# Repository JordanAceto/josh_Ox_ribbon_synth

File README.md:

# josh_Ox_ribbon_synth
Ribbon synth for [Josh Oxford](https://www.joshoxford.com/)

## Main Features 
- Single VCO with two sub-oscillators
- Transformer/diode based Ring Modulator
- Dual State-Variable Filter
- Bucket brigade Analog Delay with modulation
- Envelope VCA
- Volume VCA
- Three ADSR's
- Sample and Hold
- Flexible gate control
- Versatile Modulation Oscillator
- Ribbon controller with quantizer

## Status:

A complete synthesizer has been built with the current documents here. This instrument has been road tested on a few gigs. The current files represent a working instrument.

There are a few small PCB kludges required, and some potential future enhancements.
See the `github Issues` and `github Discussions` for little things that could be improved and an idea of what may change in the future.

The synth is constructed with semi-independent PCBs and panels for the major circuit blocks, which allows for gradually upgrading the components over time.

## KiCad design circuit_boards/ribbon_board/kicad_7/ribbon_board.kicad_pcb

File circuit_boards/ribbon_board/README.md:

# ribbon_board

## [SCHEMATIC](https://github.com/JordanAceto/josh_Ox_ribbon_synth/blob/master/circuit_boards/ribbon_board/docs/ribbon_board_schematic.pdf)

Digital ribbon controller, gate combiner, and VCA control scaler

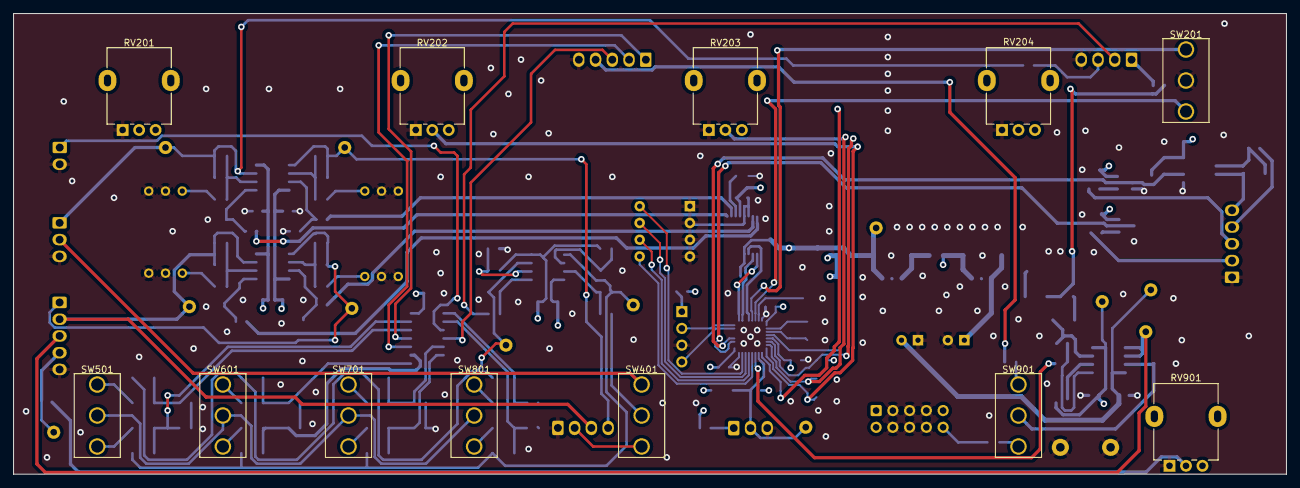
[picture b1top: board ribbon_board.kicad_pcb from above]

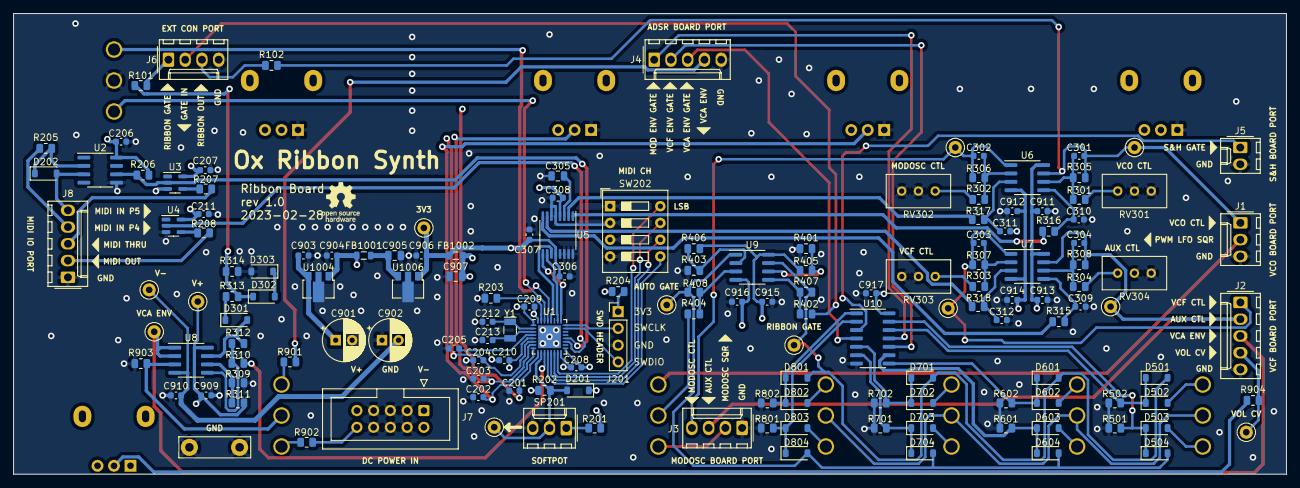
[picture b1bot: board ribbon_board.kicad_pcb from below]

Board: 4 copper layers, 193.0 x 69.8 mm, 165 parts (153 on the bottom side), 105 nets.

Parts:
C201, C202, C203, C204, C205, C206, C207, C208, C209, C210, C211, C301, C302, C303, C304, C306, C307, C308, C309, C310, C311, C312, C903, C904, C906, C909, C910, C911, C912, C913, C914, C915, C916, C917: 100n; C_0603_1608Metric
C212, C213: 4p3; C_0603_1608Metric
C305, C907: 1u; C_0805_2012Metric
C901, C902: 10u; CP_Radial_D6.3mm_P2.50mm
C905: 2u2; C_0805_2012Metric
D201: DNF; D_SOD-123
D202, D301, D501, D502, D503, D504, D601, D602, D603, D604, D701, D702, D703, D704, D801, D802, D803, D804: 1N4148W; D_SOD-123
D302, D303: 5v1; D_SOD-123
FB1001, FB1002: 100R @ 100MHz; L_0805_2012Metric
J1: VCO_port; Molex_KK-254_AE-6410-03A_1x03_P2.54mm_Vertical
J2: VCF_port; Molex_KK-254_AE-6410-05A_1x05_P2.54mm_Vertical
J3: mod_osc_port; Molex_KK-254_AE-6410-04A_1x04_P2.54mm_Vertical
J4: ADSR_port; Molex_KK-254_AE-6410-05A_1x05_P2.54mm_Vertical
J5: S&H_port; Molex_KK-254_AE-6410-02A_1x02_P2.54mm_Vertical
J6: ext_port; Molex_KK-254_AE-6410-04A_1x04_P2.54mm_Vertical
J7: power_entry; IDC-Header_2x05_P2.54mm_Vertical
J8: MIDI_IO_port; Molex_KK-254_AE-6410-05A_1x05_P2.54mm_Vertical
J201: SWD_header; PinHeader_1x04_P2.54mm_Vertical
R101, R102, R204, R313, R904: 1k; R_0805_2012Metric
R201: 22; R_0805_2012Metric
R202: DNF; R_0805_2012Metric
R203, R206, R309, R310, R401, R402, R403, R404: 10k; R_0805_2012Metric
R205: 220; R_0805_2012Metric
R207, R208: 47; R_0805_2012Metric
R301, R302, R303, R304: 20k; R_0805_2012Metric
R305, R306, R307, R308: 68k; R_0805_2012Metric
R311, R314, R405, R406, R501, R502, R601, R602, R701, R702, R801, R802, R903: 100k; R_0805_2012Metric
R312, R407, R408: 1M2; R_0805_2012Metric
R315, R316, R317, R318: 12k; R_0805_2012Metric
R901: 82k; R_0805_2012Metric
R902: 200k; R_0805_2012Metric
RV201: 10k; Potentiometer_Alpha_RD901F-40-00D_Single_Vertical
RV202, RV203, RV204: 10k c.d.; Potentiometer_Alpha_RD901F-40-00D_Single_Vertical
RV301, RV302, RV303, RV304: 5k; Potentiometer_Bourns_3296W_Vertical
RV901: 100k; Potentiometer_Alpha_RD901F-40-00D_Single_Vertical
SP201: softpot; Molex_KK-254_AE-6410-03A_1x03_P2.54mm_Vertical
SW201, SW501, SW601, SW701, SW801: SW_SPDT_MSM; SPDT_mini_toggle
SW202: MIDI_CH; SW_DIP_SPSTx04_Slide_9.78x12.34mm_W7.62mm_P2.54mm
SW401, SW901: SW_SPDT; SPDT_mini_toggle
TP201: RAW_RIBBON; TestPoint_Keystone_5000-5004_Miniature
TP301: VCO_RIBBON; TestPoint_Keystone_5000-5004_Miniature
TP302: MODOSC_RIBBON; TestPoint_Keystone_5000-5004_Miniature
TP303: VCF_RIBBON; TestPoint_Keystone_5000-5004_Miniature
TP304: AUX_CV; TestPoint_Keystone_5000-5004_Miniature
TP401: rib_gate; TestPoint_Keystone_5000-5004_Miniature
TP402: auto_gate; TestPoint_Keystone_5000-5004_Miniature
TP901: VCA_ADSR_CV; TestPoint_Keystone_5000-5004_Miniature
TP902: VCA_VOL_CV; TestPoint_Keystone_5000-5004_Miniature
TP1001: V+; TestPoint_Keystone_5000-5004_Miniature
TP1002: V-; TestPoint_Keystone_5000-5004_Miniature
TP1003: GND; TestPoint_Bridge_Pitch7.62mm_Drill1.3mm
TP1004: 3v3; TestPoint_Keystone_5000-5004_Miniature
U1: STM32L412K8Ux; QFN-32-1EP_5x5mm_P0.5mm_EP3.45x3.45mm
U2: VO0600T; SOIC-8_3.9x4.9mm_P1.27mm
U3, U4: SN74LV1T34DBV; SOT-23-5
U5: DAC8164; TSSOP-16_4.4x5mm_P0.65mm
U6, U7, U8, U9: TL072; SOIC-8_3.9x4.9mm_P1.27mm
U10: 4081; SOIC-14_3.9x8.7mm_P1.27mm
U1004: L78L05_SOT89; SOT-89-3
U1006: L78L33_SOT89; SOT-89-3
Y1: 32_768KHZ; Crystal_SMD_MicroCrystal_CC7V-T1A-2Pin_3.2x1.5mm

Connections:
+3.3V: C206.1, C207.1, C208.1, C209.1, C211.1, C306.1, C307.1, C906.1, D201.1 (K), FB1002.1, R204.1, R206.1, TP1004.1, U1.1 (VDD), U1.17 (VDD), U2.8 (VCC), U3.5 (VCC), U4.5 (VCC), U5.12 (IOVDD), U1006.1 (OUT)
+3.3VA: C210.1, C308.1, C907.1, FB1002.2, R201.1, RV201.3, RV202.3, RV203.3, RV204.3, U1.5 (VDDA), U5.4 (AVDD)
+5V: C904.1, FB1001.1, R202.1, RV901.3, U1004.1 (OUT)
+15V: C901.1, C903.1, C909.1, C911.1, C913.1, C915.1, C917.1, J7.9, J7.10, R311.2, R405.2, R406.2, R902.1, SW501.2, SW601.2, SW701.2, SW801.2, TP1001.1, U6.8 (V+), U7.8 (V+), U8.8 (V+), U9.8 (V+), U10.14 (VDD), U1004.3 (IN)
-15V: C902.2, C910.2, C912.2, C914.2, C916.2, J7.1, J7.2, TP1002.1, U6.4 (V-), U7.4 (V-), U8.4 (V-), U9.4 (V-)
/EXT_GATE_IN_NORMAL_TO_RIBBON_GATE: J6.2, R402.1
/MOD_OSC_SQR: J3.2, SW401.1 (A)
/OPT_VCF_BBD_CV: C304.2, J2.2, J3.3, R308.2, TP304.1, U7.7
/PWM_LFO_SQR: J1.2, SW401.3 (C)
/VCA_ADSR: J4.4, R901.1
/VCA_ENV_CV: J2.3, TP901.1, U8.1, U8.2 (-)
/VCA_VOL_CV: J2.4, R904.2, TP902.1
/VCO_RIBBON_CTL: C301.2, J1.1, R102.2, R305.2, TP301.1, U6.7
/digital_ribbon_control/DELAY_LEV: C204.1, RV204.2, U1.6 (PA0)
/digital_ribbon_control/GATE_3V3: R310.1, U1.11 (PA5)
/digital_ribbon_control/MIDI_CH_0: SW202.8, U1.15 (PB1)
/digital_ribbon_control/MIDI_CH_1: SW202.7, U1.14 (PB0)
/digital_ribbon_control/MIDI_CH_2: SW202.6, U1.13 (PA7)
/digital_ribbon_control/MIDI_CH_3: SW202.5, U1.12 (PA6)
/digital_ribbon_control/MIDI_IN_P4: J8.4, R205.1
/digital_ribbon_control/MIDI_IN_P5: D202.2 (A), J8.5, U2.3 (C)
/digital_ribbon_control/MIDI_OUT: J8.2, R208.2
/digital_ribbon_control/MIDI_RX: R206.2, U1.20 (PA10), U2.6 (VO), U3.2 (A)
/digital_ribbon_control/MIDI_THRU: J8.3, R207.2
/digital_ribbon_control/MIDI_TX: U1.19 (PA9), U4.2 (A)
/digital_ribbon_control/MODE_SW_1: SW201.1, U1.29 (PB6)
/digital_ribbon_control/MODE_SW_2: SW201.3, U1.30 (PB7)
/digital_ribbon_control/MODOSC_LEV: C202.1, RV202.2, U1.8 (PA2)
/digital_ribbon_control/RAW_RIBBON: D201.2 (A), R202.2, SP201.2, TP201.1, U1.10 (PA4)
/digital_ribbon_control/SPI_CS: U1.25 (PA15), U5.9 (~SYNC)
/digital_ribbon_control/SPI_SCK: U1.26 (PB3), U5.10 (SCLK)
/digital_ribbon_control/SPI_SDO: U1.28 (PB5), U5.11 (DIN)
/digital_ribbon_control/SYS_SWCLK: J201.2, U1.24 (PA14)
/digital_ribbon_control/SYS_SWDIO: J201.4, U1.23 (PA13)
/digital_ribbon_control/VCF_LEV: C203.1, RV203.2, U1.7 (PA1)
/digital_ribbon_control/VCO_LEV: C201.1, RV201.2, U1.9 (PA3)
/gate_controller/MOD_ENV_GATE: J4.1, U10.11
/gate_controller/S&H_GATE: J5.1, U10.3
/gate_controller/VCA_ADSR_gate_logic/AUTO_GATE: D504.2 (A), D604.2 (A), D704.2 (A), D804.2 (A), R408.2, TP402.1, U9.1
/gate_controller/VCA_ADSR_gate_logic/RIBBON_GATE: D501.2 (A), D601.2 (A), D701.2 (A), D801.2 (A), R407.2, TP401.1, U9.7
/gate_controller/VCA_ENV_GATE: J4.3, U10.4
/gate_controller/VCF_ENV_GATE: J4.2, U10.10
/ribbon_scalers/GATE: D302.1 (K), R101.2, R313.2, R314.1
/ribbon_scalers/MODOSC_CTL_OUT: C302.2, J3.4, R306.2, TP302.1, U6.1
/ribbon_scalers/VCF_CTL_OUT: C303.2, J2.1, R307.2, TP303.1, U7.1
GND: C201.2, C202.2, C203.2, C204.2, C205.1, C206.2, C207.2, C208.2, C209.2, C210.2, C211.2, C212.1, C213.1, C305.2, C306.2, C307.2, C308.2, C309.1, C310.1, C311.1, C312.1, C901.2, C902.1, C903.2, C904.2, C905.2, C906.2, C907.2, C909.2, C910.1, C911.2, C912.1, C913.2, C914.1, C915.2, C916.1, C917.2, D303.2 (A), J1.3, J2.5, J3.1, J4.5, J5.2, J6.4, J7.3, J7.4, J7.5, J7.6, J7.7, J7.8, J8.1, J201.3, R203.1, R309.1, R314.2, R401.1, R403.1, R501.2, R502.2, R601.2, R602.2, R701.2, R702.2, R801.2, R802.2, R903.1, RV201.1, RV202.1, RV203.1, RV204.1, RV301.2, RV301.3, RV302.2, RV302.3, RV303.2, RV303.3, RV304.2, RV304.3, RV901.1, SP201.3, SW201.2, SW202.1, SW202.2, SW202.3, SW202.4, TP1003.1, U1.16 (VSS), U1.32 (VSS), U1.33 (VSS), U2.5 (GND), U3.3 (GND), U4.3 (GND), U5.5 (VREFL), U5.6 (GND), U5.13 (A0), U5.14 (A1), U5.15 (~ENABLE), U5.16 (LDAC), U10.7 (VSS), U1004.2 (GND), U1006.2 (GND)
unnamed: D202.1 (K), R205.2, U2.2 (A)
unnamed: D301.2 (A), R312.2, U8.7
unnamed: D301.1 (K), R313.1
unnamed: D302.2 (A), D303.1 (K)
unnamed: D501.1 (K), D502.1 (K), R502.1, U10.12
unnamed: D502.2 (A), SW501.3
unnamed: D503.2 (A), SW501.1
unnamed: D503.1 (K), D504.1 (K), R501.1, U10.13
unnamed: D601.1 (K), D602.1 (K), R602.1, U10.8
unnamed: D602.2 (A), SW601.3
unnamed: D603.2 (A), SW601.1
unnamed: D603.1 (K), D604.1 (K), R601.1, U10.9
unnamed: D701.1 (K), D702.1 (K), R702.1, U10.5
unnamed: D702.2 (A), SW701.3
unnamed: D703.2 (A), SW701.1
unnamed: D703.1 (K), D704.1 (K), R701.1, U10.6
unnamed: D801.1 (K), D802.1 (K), R802.1, U10.1
unnamed: D802.2 (A), SW801.3
unnamed: D803.2 (A), SW801.1
unnamed: D803.1 (K), D804.1 (K), R801.1, U10.2
unnamed: J6.1, R101.1
unnamed: J6.3, R102.1
unnamed: J201.1, R204.2
unnamed: R301.1, RV301.1
unnamed: R302.1, RV302.1
unnamed: R303.1, RV303.1
unnamed: R304.1, RV304.1
unnamed: R904.1, RV901.2
unnamed: R201.2, SP201.1
unnamed: R404.1, SW401.2 (B)
unnamed: R902.2, SW901.1 (A)
unnamed: R903.2, SW901.2 (B), U8.3 (+)
unnamed: R901.2, SW901.3 (C)
unnamed: C205.2, U1.4 (NRST)
unnamed: C212.2, U1.2 (PC14), Y1.1
unnamed: C213.2, U1.3 (PC15), Y1.2
unnamed: R203.2, U1.31 (PH3)
unnamed: R207.1, U3.4 (Y)
unnamed: R208.1, U4.4 (Y)
unnamed: R316.1, U5.1 (VOUTA)
unnamed: R317.1, U5.2 (VOUTB)
unnamed: R318.1, U5.7 (VOUTC)
unnamed: R315.1, U5.8 (VOUTD)
unnamed: C305.1, U5.3 (VREFH/VREFOUT)
unnamed: C311.2, R317.2, U6.3 (+)
unnamed: C302.1, R302.2, R306.1, U6.2 (-)
unnamed: C310.2, R316.2, U6.5 (+)
unnamed: C301.1, R301.2, R305.1, U6.6 (-)
unnamed: C312.2, R318.2, U7.3 (+)
unnamed: C303.1, R303.2, R307.1, U7.2 (-)
unnamed: C309.2, R315.2, U7.5 (+)
unnamed: C304.1, R304.2, R308.1, U7.6 (-)
unnamed: R310.2, R312.1, U8.5 (+)
unnamed: R309.2, R311.1, U8.6 (-)
unnamed: R404.2, R408.1, U9.3 (+)
unnamed: R403.2, R406.1, U9.2 (-)
unnamed: R402.2, R407.1, U9.5 (+)
unnamed: R401.2, R405.1, U9.6 (-)
unnamed: C905.1, FB1001.2, U1006.3 (IN)

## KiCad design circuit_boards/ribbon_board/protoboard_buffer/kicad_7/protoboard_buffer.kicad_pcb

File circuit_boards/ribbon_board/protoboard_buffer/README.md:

# Protoboard Softpot Ribbon Buffer

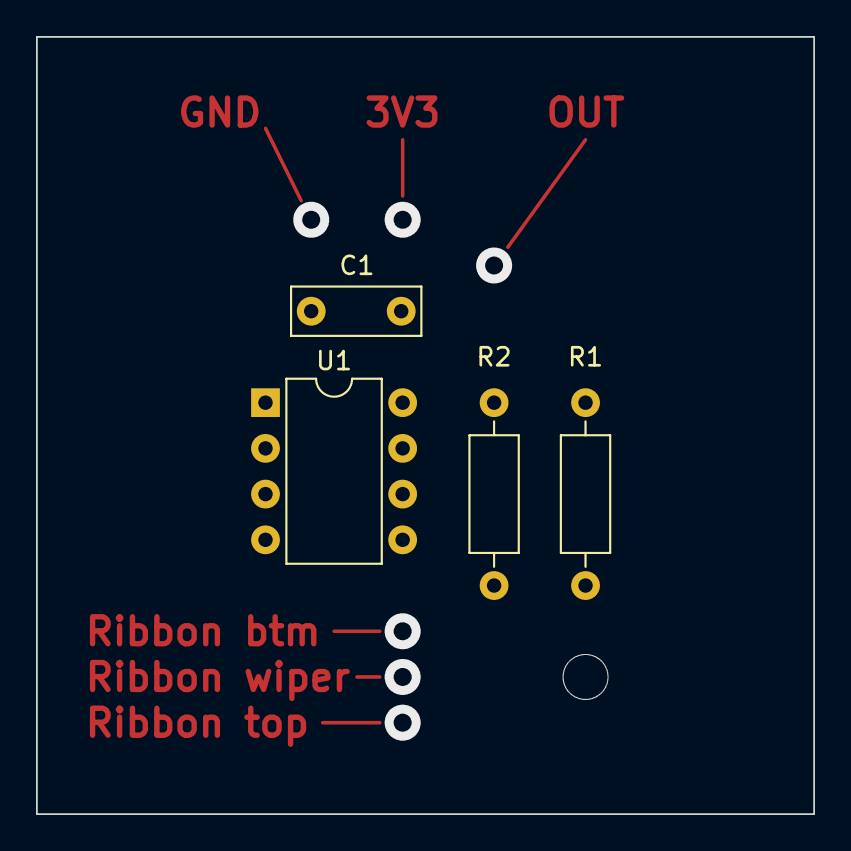
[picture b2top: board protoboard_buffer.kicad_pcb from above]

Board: 4 copper layers, 43.2 x 43.2 mm, 4 parts (0 on the bottom side), 5 nets, no tracks yet.

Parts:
C1: 100n; C_Rect_L7.0mm_W2.5mm_P5.00mm
R1: 12k; R_Axial_DIN0207_L6.3mm_D2.5mm_P10.16mm_Horizontal
R2: 1M; R_Axial_DIN0207_L6.3mm_D2.5mm_P10.16mm_Horizontal
U1: MCP6002; DIP-8_W7.62mm

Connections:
+3V3: C1.1, R1.1, R2.1, U1.8 (V+)
GND: C1.2, U1.3 (+), U1.4 (V-)
unnamed: R2.2, U1.5 (+)
unnamed: U1.6 (-), U1.7
unnamed: U1.1, U1.2 (-)

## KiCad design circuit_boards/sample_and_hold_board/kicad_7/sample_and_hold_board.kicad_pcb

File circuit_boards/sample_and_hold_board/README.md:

# Sample And Hold

## [SCHEMATIC](https://github.com/JordanAceto/josh_Ox_ribbon_synth/blob/master/circuit_boards/sample_and_hold_board/docs/sample_and_hold_board_schematic.pdf)

Basic Sample & Hold with three input mixer, noise source, and glide control.

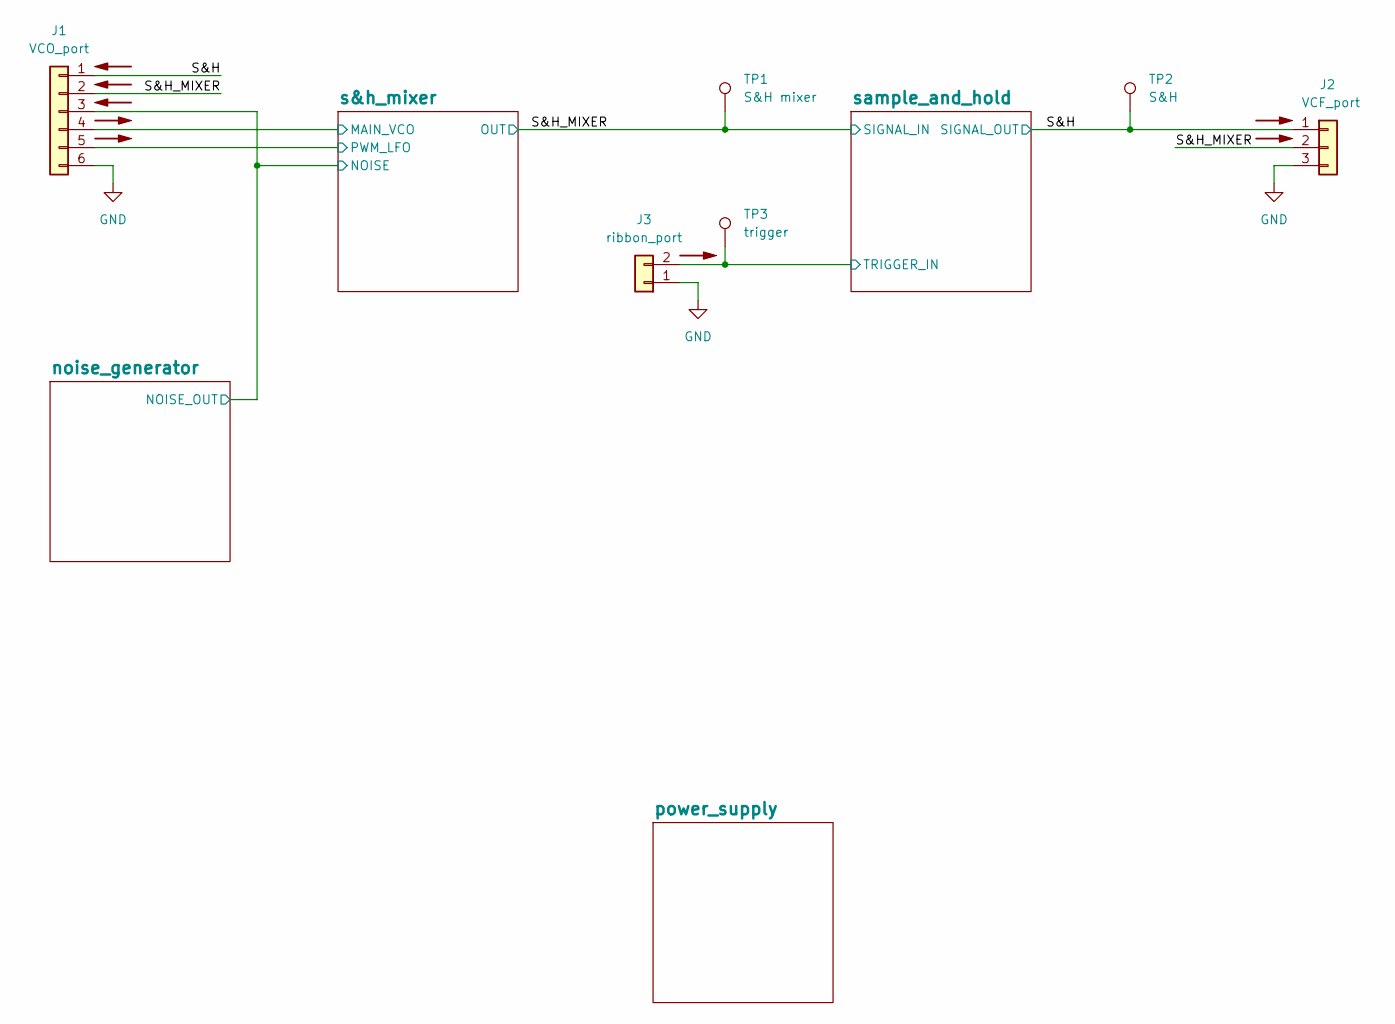
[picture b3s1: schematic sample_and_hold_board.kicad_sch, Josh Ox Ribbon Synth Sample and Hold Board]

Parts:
J1: VCO_port; Molex_KK-254_AE-6410-06A_1x06_P2.54mm_Vertical
J2: VCF_port; Molex_KK-254_AE-6410-03A_1x03_P2.54mm_Vertical
J3: ribbon_port; Molex_KK-254_AE-6410-02A_1x02_P2.54mm_Vertical
TP1: S&H mixer; TestPoint_Keystone_5000-5004_Miniature
TP2: S&H; TestPoint_Keystone_5000-5004_Miniature
TP3: trigger; TestPoint_Keystone_5000-5004_Miniature

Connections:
/S&H: J1.1, J2.1, TP2.1; also elsewhere on the board
/S&H_MIXER: J1.2, J2.2, TP1.1; also elsewhere on the board
/noise_generator/NOISE_OUT: J1.3; also elsewhere on the board
/s&h_mixer/MAIN_VCO: J1.4; also elsewhere on the board
/s&h_mixer/PWM_LFO: J1.5; also elsewhere on the board
/sample_and_hold/TRIGGER_IN: J3.2, TP3.1; also elsewhere on the board
GND: J1.6, J2.3, J3.1; also elsewhere on the board

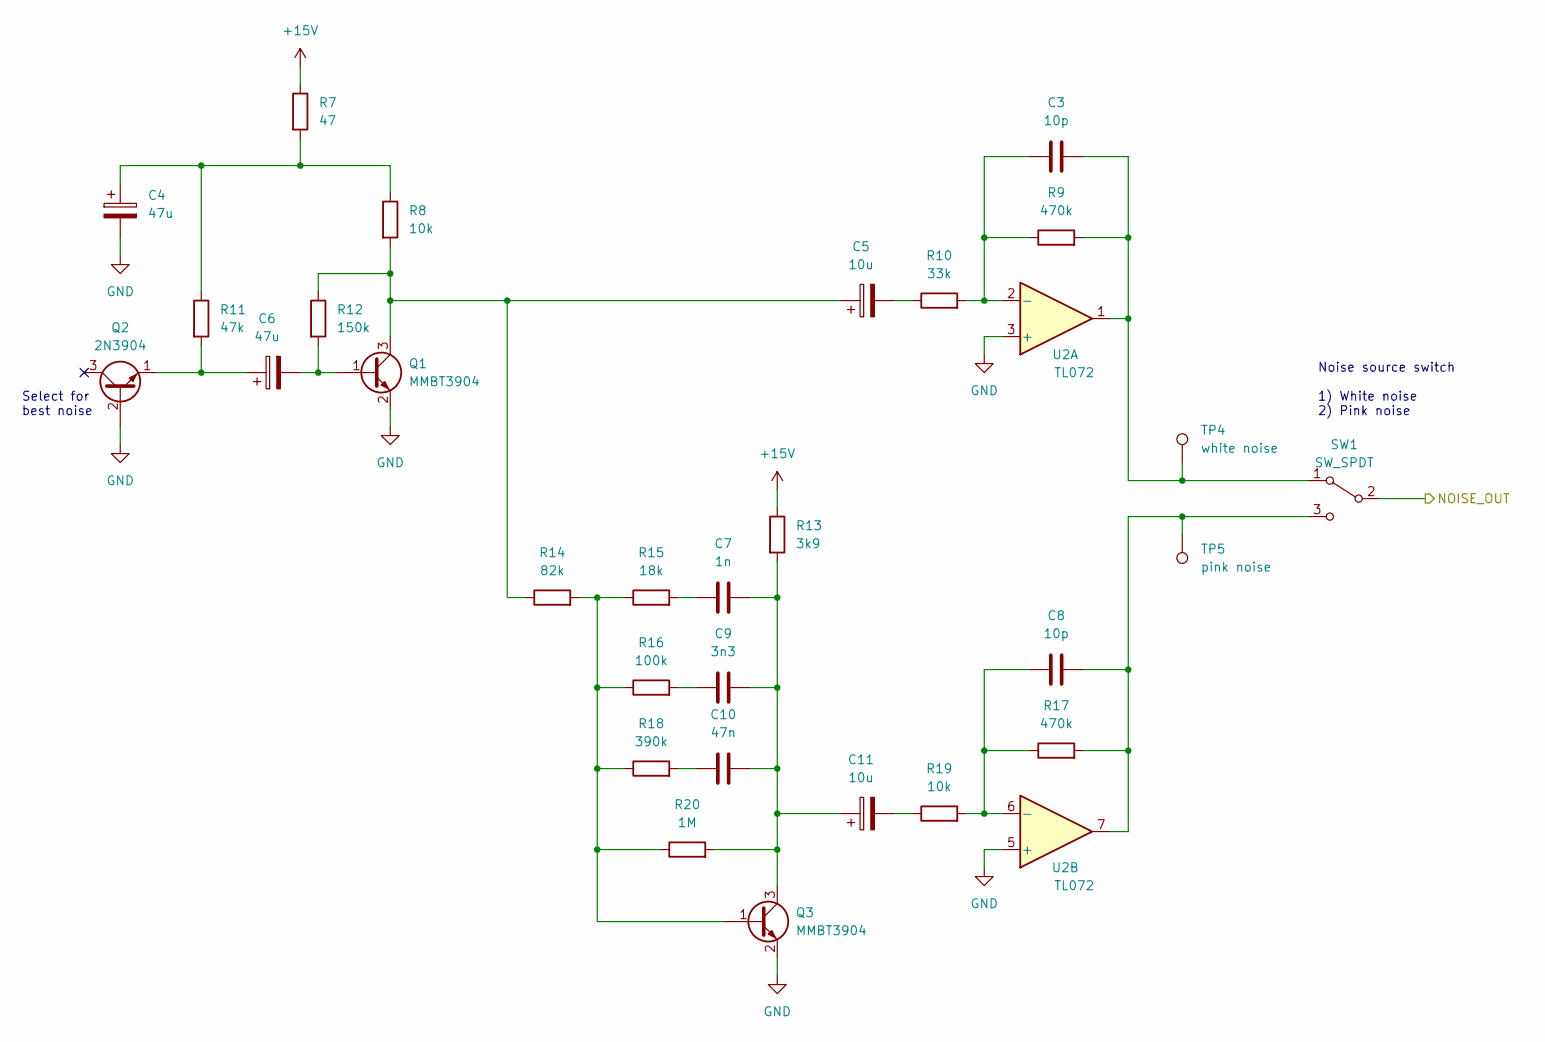
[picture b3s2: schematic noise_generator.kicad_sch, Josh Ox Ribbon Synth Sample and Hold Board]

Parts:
C3, C8: 10p; C_0805_2012Metric
C4, C6: 47u; CP_Radial_D6.3mm_P2.50mm
C5, C11: 10u; CP_Radial_D6.3mm_P2.50mm
C7: 1n; C_0805_2012Metric
C9: 3n3; C_0805_2012Metric
C10: 47n; C_0805_2012Metric
Q1, Q3: MMBT3904; SOT-23
Q2: 2N3904; TO-92_Inline_Wide
R7: 47; R_0805_2012Metric
R8, R19: 10k; R_0805_2012Metric
R9, R17: 470k; R_0805_2012Metric
R10: 33k; R_0805_2012Metric
R11: 47k; R_0805_2012Metric
R12: 150k; R_0805_2012Metric
R13: 3k9; R_0805_2012Metric
R14: 82k; R_0805_2012Metric
R15: 18k; R_0805_2012Metric
R16: 100k; R_0805_2012Metric
R18: 390k; R_0805_2012Metric
R20: 1M; R_0805_2012Metric
SW1: SW_SPDT; SPDT_mini_toggle
TP4: white noise; TestPoint_Keystone_5000-5004_Miniature
TP5: pink noise; TestPoint_Keystone_5000-5004_Miniature
U2: TL072; SO-8_5.3x6.2mm_P1.27mm

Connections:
+15V: R7.1, R13.1; also elsewhere on the board
/noise_generator/NOISE_OUT: SW1.2 (B); also elsewhere on the board
GND: C4.2, Q1.2 (E), Q2.2 (B), Q3.2 (E), U2.3 (+), U2.5 (+); also elsewhere on the board
unnamed: C3.1, R9.1, R10.2, U2.2 (-)
unnamed: C3.2, R9.2, SW1.1 (A), TP4.1, U2.1
unnamed: C4.1, R7.2, R8.1, R11.1
unnamed: C5.1, Q1.3 (C), R8.2, R12.1, R14.1
unnamed: C5.2, R10.1
unnamed: C6.1, Q2.1 (E), R11.2
unnamed: C6.2, Q1.1 (B), R12.2
unnamed: C7.1, R15.2
unnamed: C8.1, R17.1, R19.2, U2.6 (-)
unnamed: C8.2, R17.2, SW1.3 (C), TP5.1, U2.7
unnamed: C9.1, R16.2
unnamed: C10.1, R18.2
unnamed: C7.2, C9.2, C10.2, C11.1, Q3.3 (C), R13.2, R20.2
unnamed: C11.2, R19.1
unnamed: Q3.1 (B), R14.2, R15.1, R16.1, R18.1, R20.1

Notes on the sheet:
Noise source switch 1) White noise 2) Pink noise
Select for best noise

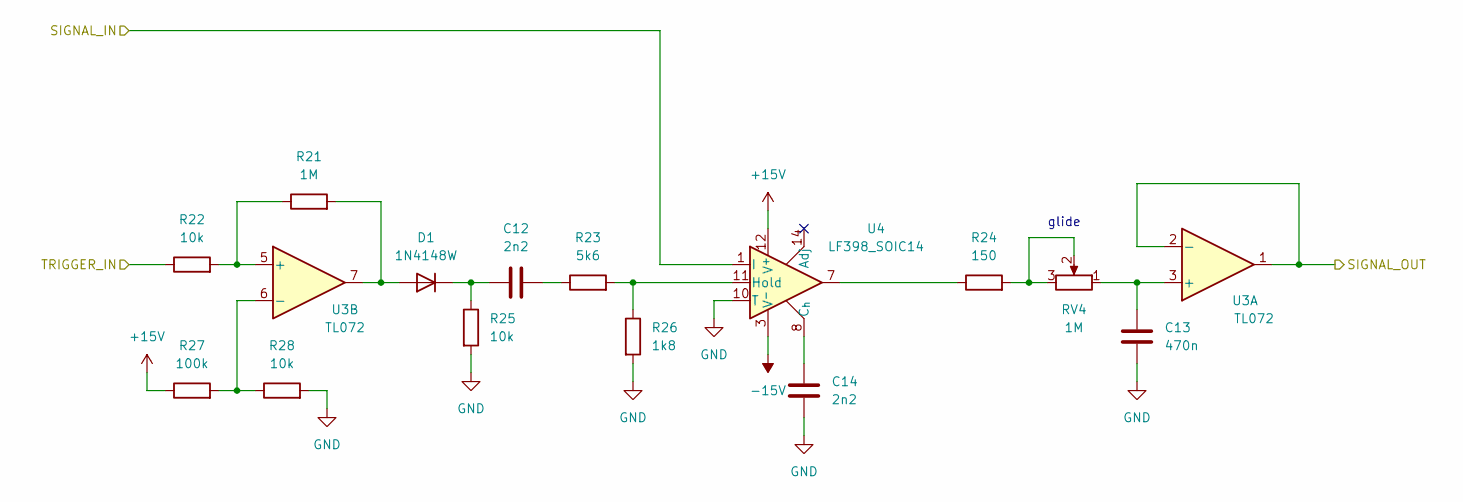
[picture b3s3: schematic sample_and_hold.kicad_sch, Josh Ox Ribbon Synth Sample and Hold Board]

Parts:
C12: 2n2; C_0805_2012Metric
C13: 470n; C_Rect_L7.2mm_W5.5mm_P5.00mm_FKS2_FKP2_MKS2_MKP2
C14: 2n2; C_Rect_L7.2mm_W2.5mm_P5.00mm_FKS2_FKP2_MKS2_MKP2
D1: 1N4148W; D_SOD-123
R21: 1M; R_0805_2012Metric
R22, R25, R28: 10k; R_0805_2012Metric
R23: 5k6; R_0805_2012Metric
R24: 150; R_0805_2012Metric
R26: 1k8; R_0805_2012Metric
R27: 100k; R_0805_2012Metric
RV4: 1M; Potentiometer_Alpha_RD901F-40-00D_Single_Vertical
U3: TL072; SO-8_5.3x6.2mm_P1.27mm
U4: LF398_SOIC14; SOIC-14_3.9x8.7mm_P1.27mm

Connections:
+15V: R27.1, U4.12 (V+); also elsewhere on the board
-15V: U4.3 (V-); also elsewhere on the board
/S&H: U3.1, U3.2 (-); also elsewhere on the board
/S&H_MIXER: U4.1 (I); also elsewhere on the board
/sample_and_hold/TRIGGER_IN: R22.1; also elsewhere on the board
GND: C13.2, C14.2, R25.2, R26.2, R28.2, U4.10 (T); also elsewhere on the board
unnamed: C12.1, D1.1 (K), R25.1
unnamed: C12.2, R23.1
unnamed: C13.1, RV4.1, U3.3 (+)
unnamed: C14.1, U4.8 (Ch)
unnamed: D1.2 (A), R21.2, U3.7
unnamed: R21.1, R22.2, U3.5 (+)
unnamed: R23.2, R26.1, U4.11 (Hold)
unnamed: R24.1, U4.7
unnamed: R24.2, RV4.2, RV4.3
unnamed: R27.2, R28.1, U3.6 (-)

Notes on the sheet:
glide

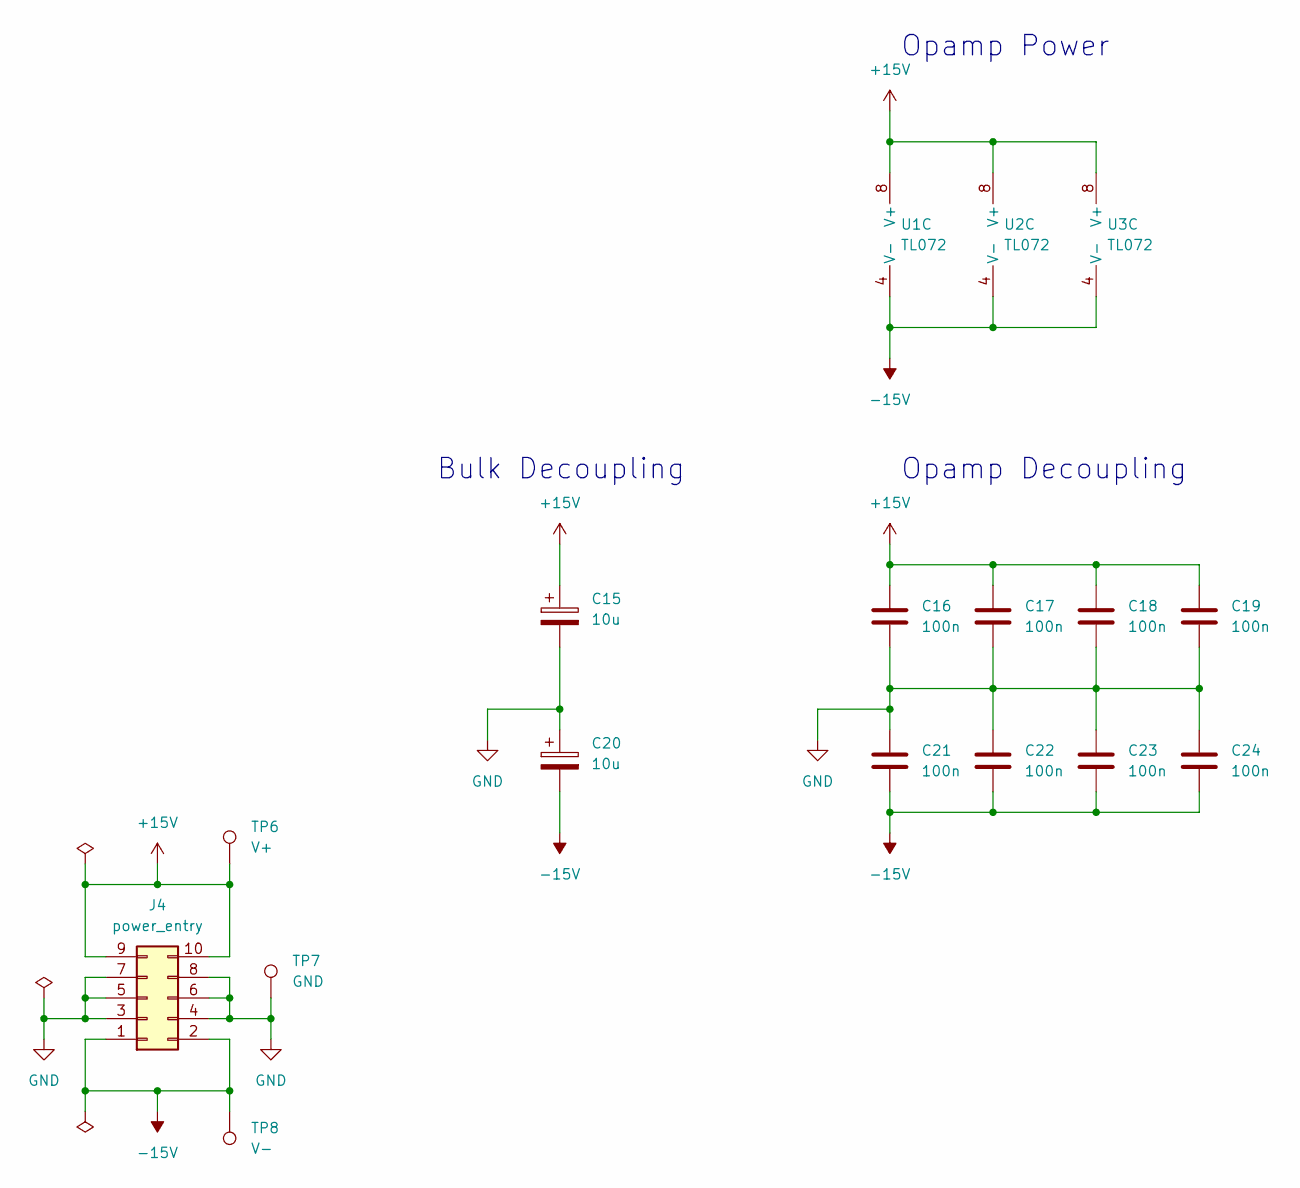
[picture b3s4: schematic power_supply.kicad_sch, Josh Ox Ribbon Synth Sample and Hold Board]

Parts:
C15, C20: 10u; CP_Radial_D6.3mm_P2.50mm
C16, C17, C18, C19, C21, C22, C23, C24: 100n; C_0805_2012Metric
J4: power_entry; IDC-Header_2x05_P2.54mm_Vertical
TP6: V+; TestPoint_Keystone_5000-5004_Miniature
TP7: GND; TestPoint_Bridge_Pitch7.62mm_Drill1.3mm
TP8: V-; TestPoint_Keystone_5000-5004_Miniature
U1, U2, U3: TL072; SO-8_5.3x6.2mm_P1.27mm

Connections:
+15V: C15.1, C16.1, C17.1, C18.1, C19.1, J4.9, J4.10, TP6.1, U1.8 (V+), U2.8 (V+), U3.8 (V+); also elsewhere on the board
-15V: C20.2, C21.2, C22.2, C23.2, C24.2, J4.1, J4.2, TP8.1, U1.4 (V-), U2.4 (V-), U3.4 (V-); also elsewhere on the board
GND: C15.2, C16.2, C17.2, C18.2, C19.2, C20.1, C21.1, C22.1, C23.1, C24.1, J4.3, J4.4, J4.5, J4.6, J4.7, J4.8, TP7.1; also elsewhere on the board

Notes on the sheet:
Opamp Decoupling
Opamp Power
Bulk Decoupling

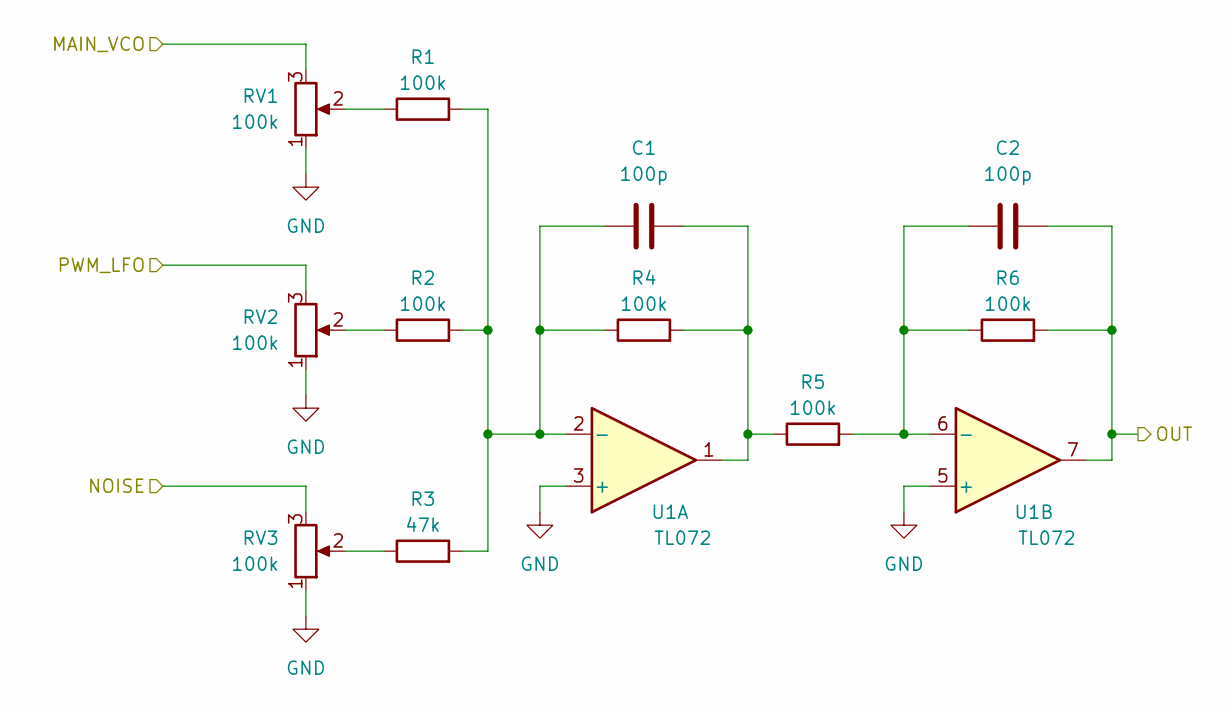
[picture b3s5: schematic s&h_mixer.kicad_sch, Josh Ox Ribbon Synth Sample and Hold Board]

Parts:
C1, C2: 100p; C_0805_2012Metric
R1, R2, R4, R5, R6: 100k; R_0805_2012Metric
R3: 47k; R_0805_2012Metric
RV1, RV2, RV3: 100k; Potentiometer_Alpha_RD901F-40-00D_Single_Vertical
U1: TL072; SO-8_5.3x6.2mm_P1.27mm

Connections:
/S&H_MIXER: C2.2, R6.2, U1.7; also elsewhere on the board
/noise_generator/NOISE_OUT: RV3.3; also elsewhere on the board
/s&h_mixer/MAIN_VCO: RV1.3; also elsewhere on the board
/s&h_mixer/PWM_LFO: RV2.3; also elsewhere on the board
GND: RV1.1, RV2.1, RV3.1, U1.3 (+), U1.5 (+); also elsewhere on the board
unnamed: C1.1, R1.2, R2.2, R3.2, R4.1, U1.2 (-)
unnamed: C1.2, R4.2, R5.1, U1.1
unnamed: C2.1, R5.2, R6.1, U1.6 (-)
unnamed: R1.1, RV1.2
unnamed: R2.1, RV2.2
unnamed: R3.1, RV3.2

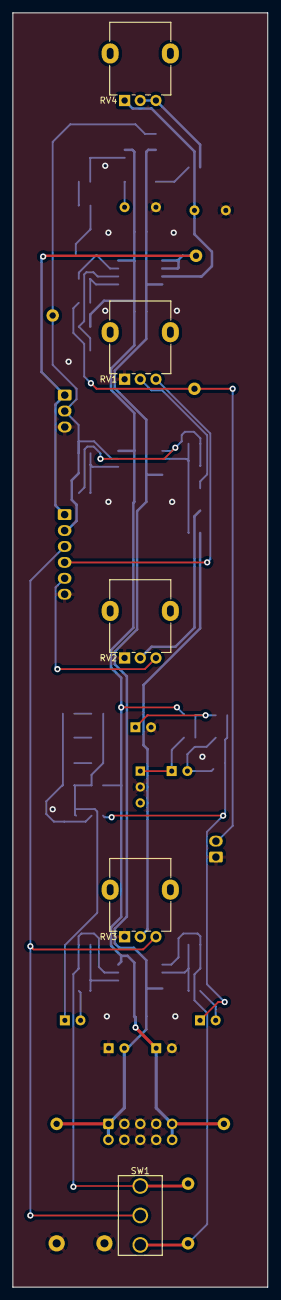
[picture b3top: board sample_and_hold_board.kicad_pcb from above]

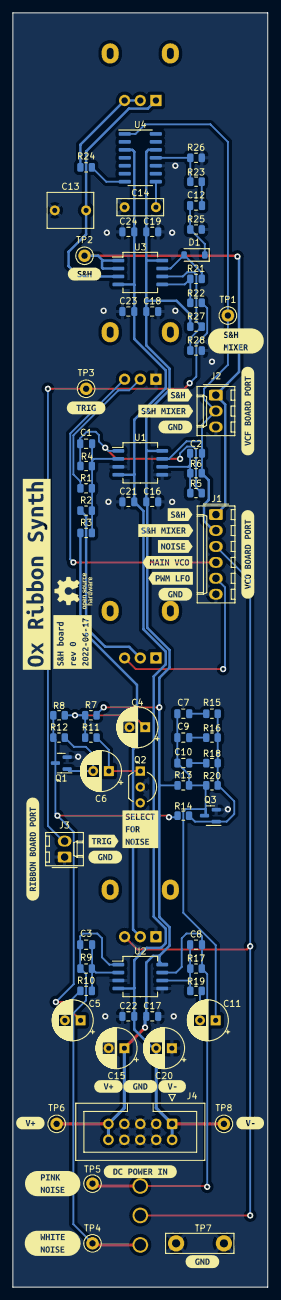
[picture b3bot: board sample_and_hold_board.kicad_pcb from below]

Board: 2 copper layers, 40.6 x 203.2 mm, 106 parts (101 on the bottom side), 40 nets.

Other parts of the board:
kibuzzard-62AC7A9F: G***; kibuzzard-62AC7A9F
kibuzzard-62AC78CB: G***; kibuzzard-62AC78CB
kibuzzard-62AC81C6: G***; kibuzzard-62AC81C6
kibuzzard-62AC81E3: G***; kibuzzard-62AC81E3
kibuzzard-62AC82BB: G***; kibuzzard-62AC82BB
kibuzzard-62AC82DF: G***; kibuzzard-62AC82DF
kibuzzard-62AC755C, kibuzzard-62AC755C#2, kibuzzard-62AC755C#3, kibuzzard-62AC755C#4, kibuzzard-62AC755C#5: G***; kibuzzard-62AC755C
kibuzzard-62AC791A, kibuzzard-62AC791A#2: G***; kibuzzard-62AC791A
kibuzzard-62AC792A, kibuzzard-62AC792A#2: G***; kibuzzard-62AC792A
kibuzzard-62AC813F, kibuzzard-62AC813F#2: G***; kibuzzard-62AC813F
kibuzzard-62AC818C: G***; kibuzzard-62AC818C
kibuzzard-62AC819F: G***; kibuzzard-62AC819F
kibuzzard-62AC822A: G***; kibuzzard-62AC822A
kibuzzard-62AC8121: G***; kibuzzard-62AC8121
kibuzzard-62AC8151, kibuzzard-62AC8151#2: G***; kibuzzard-62AC8151
kibuzzard-62AC8170: G***; kibuzzard-62AC8170
kibuzzard-62AC8211: G***; kibuzzard-62AC8211
kibuzzard-62AC8240: G***; kibuzzard-62AC8240
kibuzzard-62AC8254: G***; kibuzzard-62AC8254
kibuzzard-62AC8271: G***; kibuzzard-62AC8271
kibuzzard-62AC8282: G***; kibuzzard-62AC8282

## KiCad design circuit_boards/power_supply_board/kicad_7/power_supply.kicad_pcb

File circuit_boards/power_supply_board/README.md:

# Power Supply Board

## [SCHEMATIC](https://github.com/JordanAceto/josh_Ox_ribbon_synth/blob/master/circuit_boards/power_supply_board/docs/power_supply_schematic.pdf)

This is an unremarkable LM317/LM337 based bipolar 15 volt DC supply which supplies power to the rest of the system.

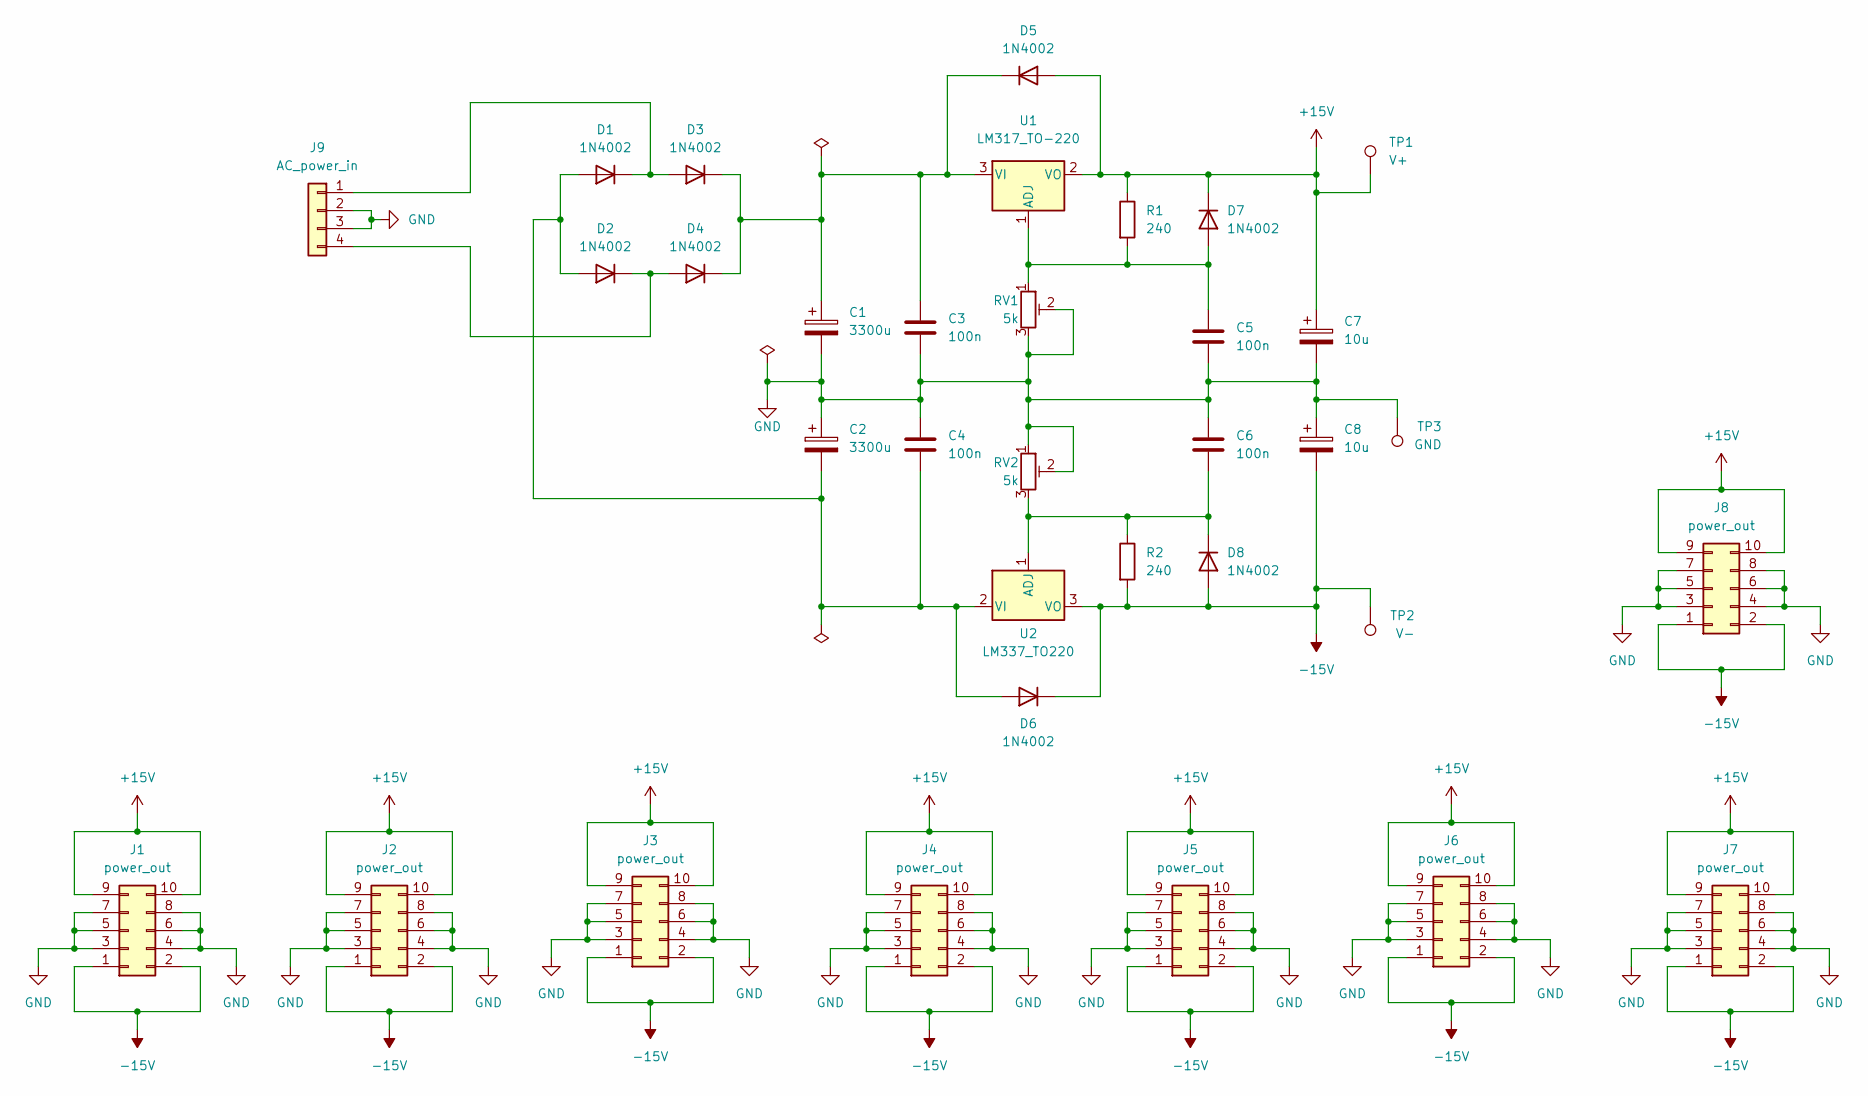
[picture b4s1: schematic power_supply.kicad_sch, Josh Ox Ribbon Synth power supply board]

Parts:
C1, C2: 3300u; CP_Radial_D18.0mm_P7.50mm
C3, C4, C5, C6: 100n; C_Rect_L7.0mm_W2.5mm_P5.00mm
C7, C8: 10u; CP_Radial_D6.3mm_P2.50mm
D1, D2, D3, D4, D5, D6, D7, D8: 1N4002; D_DO-41_SOD81_P10.16mm_Horizontal
J1, J2, J3, J4, J5, J6, J7, J8: power_out; IDC-Header_2x05_P2.54mm_Vertical
J9: AC_power_in; Molex_Mini-Fit_Jr_5566-04A_2x02_P4.20mm_Vertical
R1, R2: 240; R_Axial_DIN0207_L6.3mm_D2.5mm_P10.16mm_Horizontal
RV1, RV2: 5k; Potentiometer_Bourns_3296W_Vertical
TP1: V+; TestPoint_Keystone_5000-5004_Miniature
TP2: V-; TestPoint_Keystone_5000-5004_Miniature
TP3: GND; TestPoint_Bridge_Pitch7.62mm_Drill1.3mm
U1: LM317_TO-220; TO-220-3_Vertical
U2: LM337_TO220; TO-220-3_Vertical

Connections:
+15V: C7.1, D5.2 (A), D7.1 (K), J1.9, J1.10, J2.9, J2.10, J3.9, J3.10, J4.9, J4.10, J5.9, J5.10, J6.9, J6.10, J7.9, J7.10, J8.9, J8.10, R1.1, TP1.1, U1.2 (VO)
-15V: C8.2, D6.1 (K), D8.2 (A), J1.1, J1.2, J2.1, J2.2, J3.1, J3.2, J4.1, J4.2, J5.1, J5.2, J6.1, J6.2, J7.1, J7.2, J8.1, J8.2, R2.2, TP2.1, U2.3 (VO)
GND: C1.2, C2.1, C3.2, C4.1, C5.2, C6.1, C7.2, C8.1, J1.3, J1.4, J1.5, J1.6, J1.7, J1.8, J2.3, J2.4, J2.5, J2.6, J2.7, J2.8, J3.3, J3.4, J3.5, J3.6, J3.7, J3.8, J4.3, J4.4, J4.5, J4.6, J4.7, J4.8, J5.3, J5.4, J5.5, J5.6, J5.7, J5.8, J6.3, J6.4, J6.5, J6.6, J6.7, J6.8, J7.3, J7.4, J7.5, J7.6, J7.7, J7.8, J8.3, J8.4, J8.5, J8.6, J8.7, J8.8, J9.2, J9.3, RV1.2, RV1.3, RV2.1, RV2.2, TP3.1
unnamed: C1.1, C3.1, D3.1 (K), D4.1 (K), D5.1 (K), U1.3 (VI)
unnamed: C2.2, C4.2, D1.2 (A), D2.2 (A), D6.2 (A), U2.2 (VI)
unnamed: C5.1, D7.2 (A), R1.2, RV1.1, U1.1 (ADJ)
unnamed: C6.2, D8.1 (K), R2.1, RV2.3, U2.1 (ADJ)
unnamed: D1.1 (K), D3.2 (A), J9.1
unnamed: D2.1 (K), D4.2 (A), J9.4

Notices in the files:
circuit_boards/ADSR_board/kicad_6/ADSR.kicad_sch:
creativecommons.org/licences/by/4.0
license: CC by 4.0
circuit_boards/ADSR_board/kicad_7/ADSR.kicad_sch:
creativecommons.org/licenses/by/4.0
